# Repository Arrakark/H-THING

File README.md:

# H-THING

An H-Bridge circuit for controlling a single robot motor.

## PCB Description

### Specs

* 5V - 17V motor voltage range
* To be used with <1000Hz switching freqnuency (500Hz is preferred)
* Supports 3.3v and 5.0v logic level inputs
* Capable of driving up to 3A
* Requires only one PWM pin for speed, one digial I/O for direction
* Can be used as a half-bridge if direction pin is disconnected
* Has space for a current-sensing resistor (R6)
* **Cannot be used to coast the motor**

This project was created using KiCad 5 RC2. Use it to open and edit this design.

### BOM

| "Id" | "Designator"      | "Package"                                        | "Quantity" | "Designation"           | "Supplier and ref" |  |  | 
|------|-------------------|--------------------------------------------------|------------|-------------------------|--------------------|--|--| 
| 1    | "MH3,MH2,MH4,MH1" | "MountingHole_3.2mm_M3"                          | 4          | "MountingHole_3.2mm_M3" |                    |  |  | 
| 2    | "C1,C3"           | "C_Disc_D5.0mm_W2.5mm_P5.00mm"                   | 2          | "100nF"                 |                    |  |  | 
| 3    | "C2"              | "CP_Radial_D10.0mm_P5.00mm"                      | 1          | "470uF"                 |                    |  |  | 
| 4    | "J1"              | "TerminalBlock_bornier-2_P5.08mm"                | 1          | "MOTOR_CON"             |                    |  |  | 
| 5    | "J2"              | "TerminalBlock_bornier-2_P5.08mm"                | 1          | "PWR_PASSTHRU"          |                    |  |  | 
| 6    | "J3"              | "TerminalBlock_bornier-2_P5.08mm"                | 1          | "MAIN_PWR"              |                    |  |  | 
| 7    | "Q1,Q6"           | "TO-92_Inline_Narrow_Oval"                       | 2          | "2N3904"                |                    |  |  | 
| 8    | "R1,R2,R4,R5"     | "R_Axial_DIN0207_L6.3mm_D2.5mm_P2.54mm_Vertical" | 4          | "1k00"                  |                    |  |  | 
| 9    | "J4"              | "Socket_Strip_Straight_1x03_Pitch2.54mm"         | 1          | "SIG_CON"               |                    |  |  | 
| 10   | "Q2,Q4"           | "TO-220-3_Vertical"                              | 2          | "IRF5305"               |                    |  |  | 
| 11   | "Q3,Q5"           | "TO-220-3_Vertical"                              | 2          | "HUF75321"              |                    |  |  | 
| 12   | "R6"              | "R_Axial_DIN0207_L6.3mm_D2.5mm_P2.54mm_Vertical" | 1          | "0R20"                  |                    |  |  | 
| 13   | "G***"            | "rover"                                          | 1          | "LOGO"                  |                    |  |  | 

## Installing

Install the H-THING using standoffs on the robot. Apply motor power (5-17V) to the screw terminals on the right hand side. **Make sure the polarity is correct!** The other screw terminal is for power pass-trough. Use the passthrough to chain more H-THINGs together. Finally, connect the motor to the last screw terminal (the one with the motor label).

Connect the H-THING to a microcontroller by connecting one of the outermost pins to a PWM pin, and the other to a digital I/O (non PWM).

## Signal Control

Use the library included with this repo to control the speed and direction of the motor. 

Use the following code to create a H-THING object:
```
#define SPEED_PIN 9 
#define DIR_PIN 3 
HTHING leftm = HTHING(PA3,PA2);
```
To control the motor:
```
left_motor.stop(); //stops the motor
left_motor.run(-255); //runs the motor backwards
left_motor.run(120); //runs the motor forwards
```

## License

This project is licensed under the MIT License - see the [LICENSE.md](https://github.com/Arrakark/H-THING/blob/master/LICENSE) file for details

## Acknowledgments

* Special thanks to the V2FC robot team!

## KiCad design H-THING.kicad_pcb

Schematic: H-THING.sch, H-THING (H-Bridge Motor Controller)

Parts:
C1, C3: 100nF; C_Disc_D5.0mm_W2.5mm_P5.00mm
C2: 470uF; CP_Radial_D10.0mm_P5.00mm
J1: MOTOR_CON; TerminalBlock_bornier-2_P5.08mm
J2: PWR_PASSTHRU; TerminalBlock_bornier-2_P5.08mm
J3: MAIN_PWR; TerminalBlock_bornier-2_P5.08mm
J4: SIG_CON; PinSocket_1x03_P2.54mm_Vertical
Q1, Q6: 2N3904; TO-92_Inline
Q2, Q4: IRF5305; TO-220-3_Vertical
Q3, Q5: HUF75321; TO-220-3_Vertical
R1, R2, R4, R5: 1k00; R_Axial_DIN0207_L6.3mm_D2.5mm_P2.54mm_Vertical
R6: 0R20; R_Axial_DIN0207_L6.3mm_D2.5mm_P2.54mm_Vertical

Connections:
/HB1: J4.1, R1.2
/HB2: J4.3, R5.1
/I_SENSE: J4.2, Q3.3, Q5.3, R6.1
GND: C2.2, C3.2, J2.1, J3.2, Q1.1 (E), Q6.1 (E), R6.2
unnamed: C1.1, J1.1, Q4.2, Q5.2
unnamed: C1.2, J1.2, Q2.2, Q3.2
unnamed: Q1.2 (B), R1.1
unnamed: Q1.3 (C), Q2.1, Q3.1, R2.2
unnamed: Q4.1, Q5.1, Q6.3 (C), R4.2
unnamed: Q6.2 (B), R5.2
VCC: C2.1, C3.1, J2.2, J3.1, Q2.3, Q4.3, R2.1, R4.1

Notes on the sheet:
H-Bridge
Power Connection
Signal Connection
Using I_SENSE: PCB trace between GND and halfbridge acts as resistor. Read I_SENSE using an analogRead and correlate with motor current. Bypass feature by placing R3 (use wire).
Reverse connector to reverse motor direction

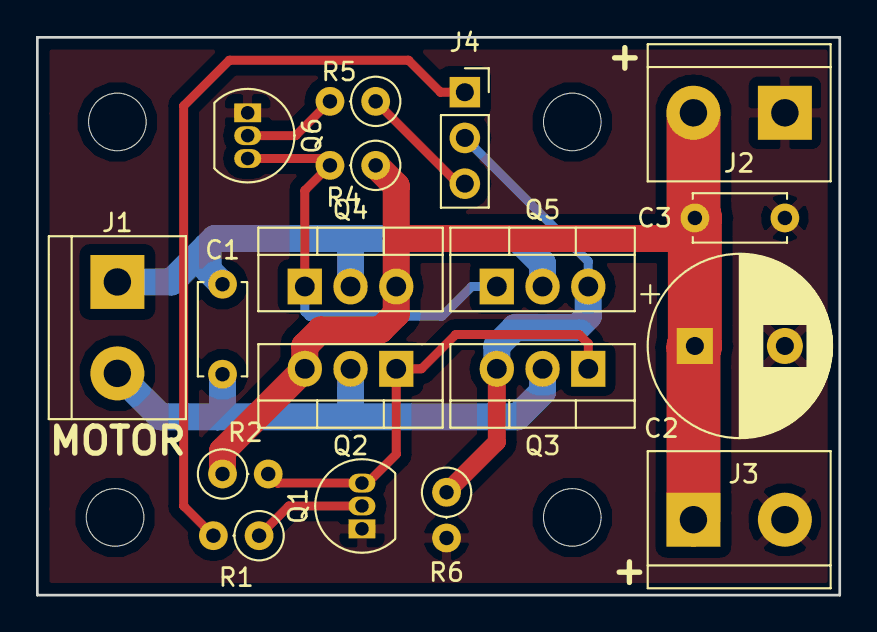
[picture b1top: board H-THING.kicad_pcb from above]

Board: 2 copper layers, 44.6 x 31.0 mm, 22 parts (0 on the bottom side), 11 nets.

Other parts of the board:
MH1, MH2, MH3, MH4: MountingHole_3.2mm_M3

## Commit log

2018-06-08 init
2018-06-08 Finished schematic, started PCB
2018-06-08 Layed out PCB
2018-06-09 Added images
2018-06-09 Added FAB files
2018-06-12 Added propper grbr outputs
2018-06-12 Added lib
2018-06-12 Added lib explaination
2018-06-30 Updated 3d model with components
2018-07-05 Added new WORKING library
2018-07-05 Updated readme to remove unused commands
